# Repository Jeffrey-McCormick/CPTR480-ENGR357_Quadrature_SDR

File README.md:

# CPTR480 Quadrature SDR Hardware Documentation

This repository contains the KiCad schematics, PCB layouts, and Bills of Materials for the CPTR480 Quadrature Software Defined Radio (SDR) receiver board designed by Jeffrey McCormick and Daniel Mendoza for ENGR357 and CPTR480.

**Other contributors**: Riley Smith, Joshua Garbi

## System Architecture

The radio is a direct-conversion, quadrature-sampling receiver (commonly utilizing a Tayloe Detector topology) managed by a Raspberry Pi Pico. The RF front-end downconverts the incoming antenna signal directly to baseband I (In-phase) and Q (Quadrature) audio signals, which are digitized and processed by the RP2040 microcontroller. The board also includes other parts like rotary encoder, OLED display, SD card reader, and DAC for audio output for added functionality. The radio is designed work both on battery power as well as USB power through the Raspberry Pi Pico. The board is designed to be portable and hand-held. 

### Core Hardware Modules

1. **Microcontroller & Digital Core**
   - **Raspberry Pi Pico (RP2040)**: The brains of the SDR. Handles I2C UI/Hardware control, I2S digital audio streams, DSP, and SD card interfacing. The board will support both the original Raspberry Pi Pico board varients and the YD2040 from CPTR480. 

2. **RF Front-End & Mixing (Tayloe Detector)**
   - **SN74CBT3253CDBR**: Dual 1-of-4 FET Multiplexer/Demultiplexer. This high-speed analog switch acts as the quadrature mixer, sequentially sampling the incoming RF signal at the Local Oscillator frequency to produce differential baseband I and Q signals. A second SN74CBT was used for RF filter switching in the front-end.   

   - **SN74AC74DR**: Dual D-Type Positive-Edge-Triggered Flip-Flop, typically used to accurately divide the synthesized clock to drive the Tayloe detector switches with precise 90-degree phase offsets.

3. **Clock Generation**
   - **Si5351A-B-GT**: I2C-programmable ANY-frequency CMOS clock generator. Driven by a high-precision **24.576 MHz TCXO** (ASTX-H11) for ultra-low drift, it synthesizes the Local Oscillator (LO) frequencies. For quadrature mixing, it is configured to output signals at 4x the target listen frequency.

4. **Baseband Amplification**
   - **INA821ID**: High-precision instrumentation amplifiers used to convert the differential outputs of the Tayloe mixer to single-ended signals and apply initial low-noise gain.
   - **OPA1612AxD**: Dual SoundPlus™ high-performance bipolar-input audio operational amplifiers for active low-pass filtering and final baseband gain stages.

5. **Data Converters (Audio/Baseband)**
   - **PCM1808PWR**: 24-bit, 96-kHz Stereo ADC. Digitizes the analog I and Q baseband signals and sends them to the Pico over I2S.
   - **PCM5102A**: 32-bit, 384-kHz Stereo DAC with integrated PLL. Converts the final DSP-processed audio or playback audio from the Pico back to analog for the headphone output.

6. **User Interface**
   - **0.96" OLED Display**: 128x64 pixels, I2C interface.
   - **Rotary Encoder (Alps EC11)**: Includes a push-button switch for frequency tuning and menu navigation.
   - **Tactile Button**: For additional UI control inputs.

7. **Power Management**
   - **TPS7A2045PDQN**: 4.5V Ultra-Low-Noise LDO regulator for sensitive analog components.
   - **TPS72733DSER**: 3.3V Low-Dropout regulator for clean digital/mixed-signal voltage rails.

8. **Connectivity**
   - **BNC Connector (Amphenol)**: Main RF antenna input.
   - **3.5mm Audio Jacks (CUI SJ-3523-SMT)**: For SDR audio output and DAC direct output.
   - **MicroSD Card Slot**: Connected via SPI for playing WAV files or potentially recording IQ streams.

## KiCad Project Structure

The hardware source files are located in the `Radio_Receiver_McCormick_Mendoza` directory. The schematic is built hierarchically:

- **`Radio_Receiver_McCormick_Mendoza.kicad_sch`**: The top-level schematic tying all functional blocks together.
- **`antenna.kicad_sch` / `low_pass_filter.kicad_sch`**: Front-end filtering blocks.
- **`mixer.kicad_sch`**: The Tayloe detector and RF switching core.
- **`clock_generator.kicad_sch`**: Si5351 synthesizer and TCXO.
- **`ADC-24bit.kicad_sch` / `Audio_DAC.kicad_sch`**: Data converter sub-sheets.
- **`raspberry_pi_pico.kicad_sch`**: MCU pinning and decoupling.
- **`power_supply.kicad_sch`**: LDOs and power distribution network.
- **`Display.kicad_sch` / `Angle_Encoder.kicad_sch`**: UI peripherals.

### PCB Images

### Bill of Materials (BOM)

The complete component list, including LCSC part numbers for JLCPCB assembly, can be found in `Radio_Receiver_McCormick_Mendoza.csv`.

## Bring-up and Testing Order

Standalone scripts used during hardware validation. Each can be uploaded and run independently on the board.

| Component | File | Function | Pass/Fail |
|-----------|------|----------|-----------|
| LED | `Bringup/led_blink.py` | Blinks GPIO5 to confirm basic GPIO and upload toolchain | &check; |
| I2C bus | `Bringup/i2c_scan.py` | Scans I2C0 (SDA=12, SCL=13); expects Si5351 at `0x60`, OLED at `0x3C` | &check; |
| OLED display | `Bringup/oled_test.py` | Full exercise suite for the SSD1306 (text, lines, animation, contrast, power cycle) via `ssd1306.py` | &check; |
| Rotary encoder + button | `Bringup/rotary_encoder.py` | `QuadratureEncoder` (detent counting on GPIO 20/21) and `ButtonHandler` (debounced click + long-press on GPIO 22) | &check; |
| Si5351 clock | `Bringup/si5351_test.py` | Register R/W test, PLL lock check, 10.24 MHz quadrature setup, frequency sweep with integer-divider validation | &check; |
| Filter MUX | `Bringup/filter_mux_control.py` | Drives CTL1 (GPIO19) and CTL2 (GPIO18) to select one of four analog filter paths | &check; |
| Si5351 driver | `Bringup/Load_files/si5351.py` | I2C driver: PLL/multiplier config, per-clock dividers, phase offset, output enable | &check; |
| OLED driver | `Bringup/Load_files/ssd1306.py` | Standard MicroPython SSD1306 I2C framebuffer driver | &check; |
| DAC | `Bringup/dac.py` | I2S driver: Configure DAC for stereo or mono playback at 44.1 kHz | &check; |
| ADC | `Bringup/adc.py` | I2S driver: Configure ADC for 16-bit stereo sampling | &cross; |
|  ADC Integration | `Bringup/adc_test.py` | Full duplex loopback test: DAC outputs a sine wave, ADC reads it back, and an LED toggles based on amplitude | &cross; |

**`si5351_test.py` details:** Configures PLLA with N=25 (VCO = 24.576 MHz × 25 = 614.4 MHz), sets CLK0/1/2 dividers, and applies phase offsets of 0°, 90°, and 180° via `set_phase()`. The `is_integer_divider()` helper ensures only frequencies that divide the VCO evenly are programmed during the sweep.

**`rotary_encoder.py` details:** Encoder uses IRQ-driven quadrature decoding with detent aggregation (`ppr` parameter). `ButtonHandler` distinguishes short click (on release before 600 ms) from long press (held ≥ 600 ms); the main app uses long press for "back" navigation.
### Images

## Results

Base Goals

- [x]  Minimum Discernable signal less than 1uV
  - Achieved 1mV
- [ ]  Switching between AM and HF bands
  - Only tested for AM band. 
- [x]  Intuitive interface
  - Got it. See /Software 
- [x]  Portability
   - Battery power works well. Antenna and Board grounds have to be tied together for portable antenna grounding
- [x]  Dual power mode (battery and usb)
   - Got it!! Both work as intended.

 Reach Goals:

- [x]  Low noise (-60dB)
  - Achieved -90dB
  
- [/]  High Image Rejection (-20dB)
- Achieved -15dB to -25dB depending on individual resistor pairs. 
- [ ]  Can record radio signals
   - Unable to test 

### Images

## Future Work

- [ ] Input I and Q signls into pico via ADC 
   - ADC verification 
- [ ] Tracelength matching for Q_LO and I_LO
- [ ] Manufacture optional LP and BP Filters
- [ ] RF signal processing software

### Optional
- [ ] Adding option for lower gain in Intrumentation Amplifier.

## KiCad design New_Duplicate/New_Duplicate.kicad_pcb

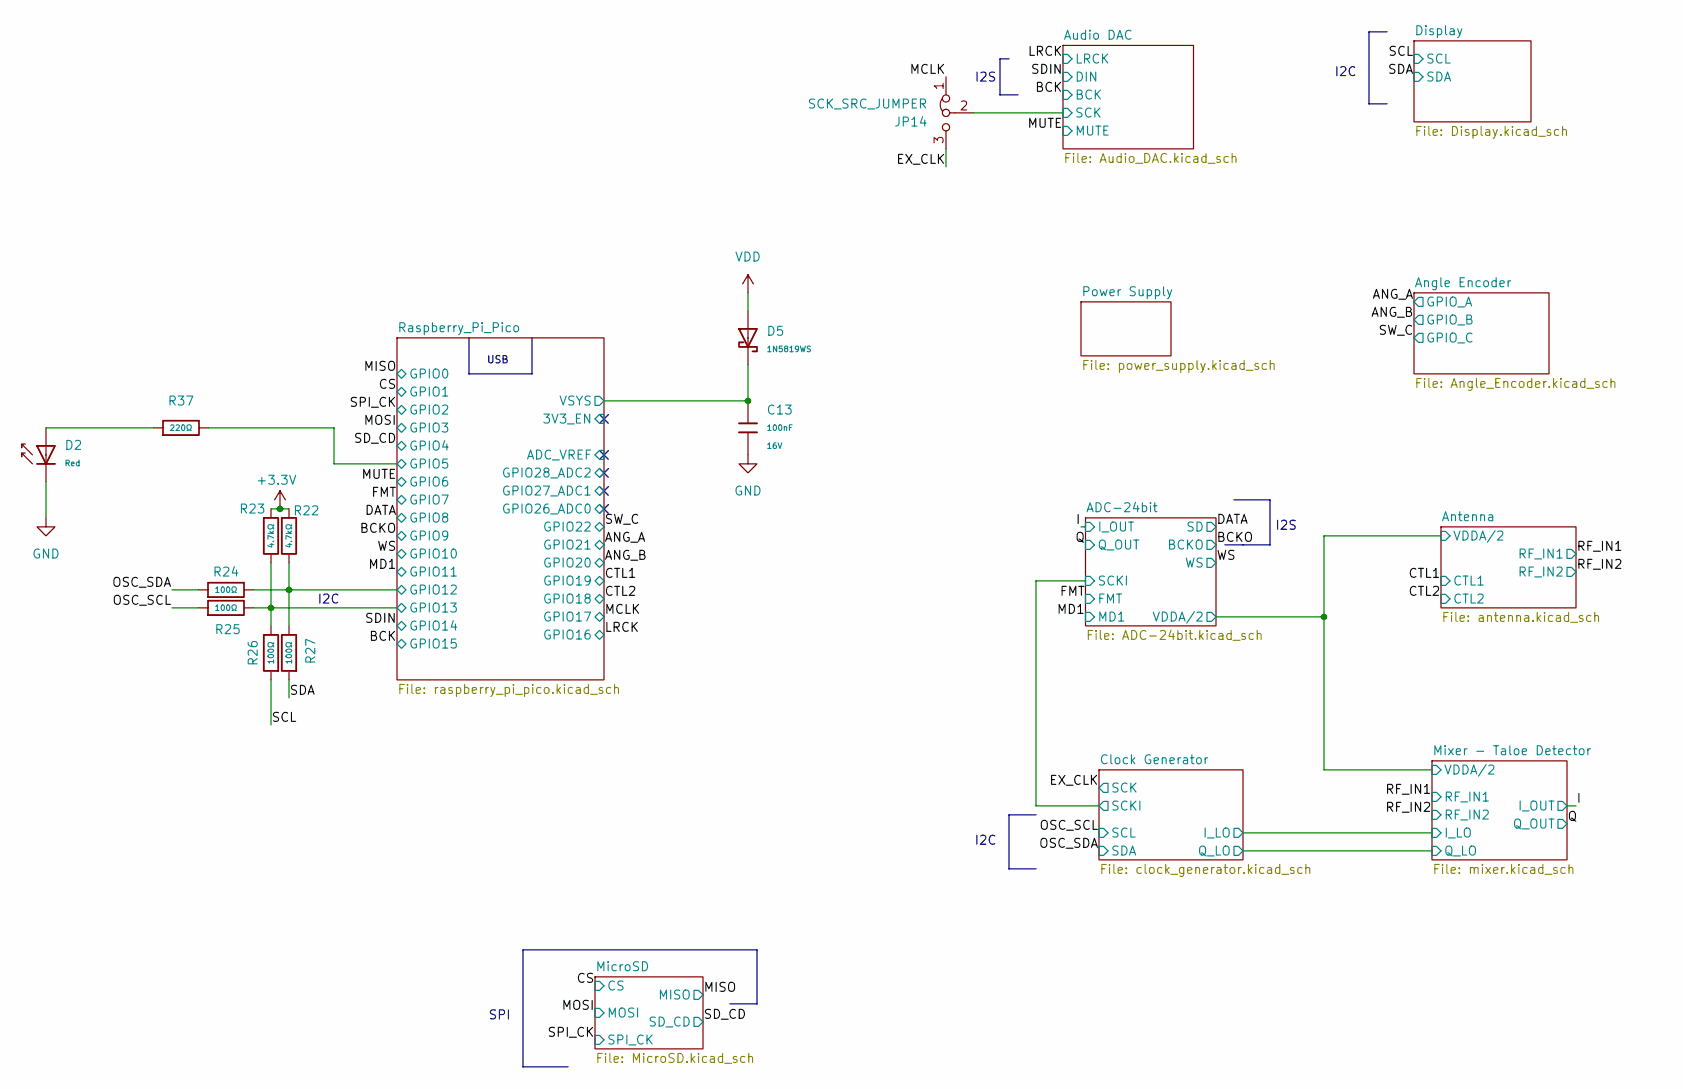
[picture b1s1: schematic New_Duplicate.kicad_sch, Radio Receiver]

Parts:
C13: 100nF; C_0402; Voltage Rated 16V; Tolerance ±10%; Part CL05B104KO5NNNC; LCSC C1525
D2: Red; D_0805; Forward Voltage (VF) 1.6V~2.6V; Part NCD0805R1; LCSC C84256
D5: 1N5819WS; D_SOD-323; Forward Voltage (Vf@If) 600mV@1A; Reverse Voltage (Vr) 40V; Part 1N5819WS; LCSC C191023
JP14: SCK_SRC_JUMPER; SolderJumper-3_P1.3mm_Bridged2Bar12_RoundedPad1.0x1.5mm_Num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
R22, R23: 4.7kΩ; R_0805; Overload Voltage (Max) 150V; Tolerance ±1%; Part 0805W8F4701T5E; LCSC C17673
R24, R25, R26, R27: 100Ω; R_0805; Overload Voltage (Max) 150V; Tolerance ±1%; Part 0805W8F1000T5E; LCSC C17408
R37: 220Ω; R_0603; Overload Voltage (Max) 75V; Tolerance ±1%; Part 0603WAF2200T5E; LCSC C22962

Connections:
+3.3V: R22.1, R23.1; also elsewhere on the board
/Audio DAC/SCK: JP14.2 (C); also elsewhere on the board
/EX_CLK: JP14.3 (B); also elsewhere on the board
/MCLK: JP14.1 (A); also elsewhere on the board
/OSC_SCL: R25.1; also elsewhere on the board
/OSC_SDA: R24.1; also elsewhere on the board
/Raspberry_Pi_Pico/GPIO5: R37.2; also elsewhere on the board
/Raspberry_Pi_Pico/GPIO12: R22.2, R24.2, R27.2; also elsewhere on the board
/Raspberry_Pi_Pico/GPIO13: R23.2, R25.2, R26.2; also elsewhere on the board
/Raspberry_Pi_Pico/VSYS: C13.1, D5.1; also elsewhere on the board
/SCL: R26.1; also elsewhere on the board
/SDA: R27.1; also elsewhere on the board
unnamed: D2.2, R37.1
VDD: D5.2; also elsewhere on the board

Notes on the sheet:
I2S
USB
I2C
SPI

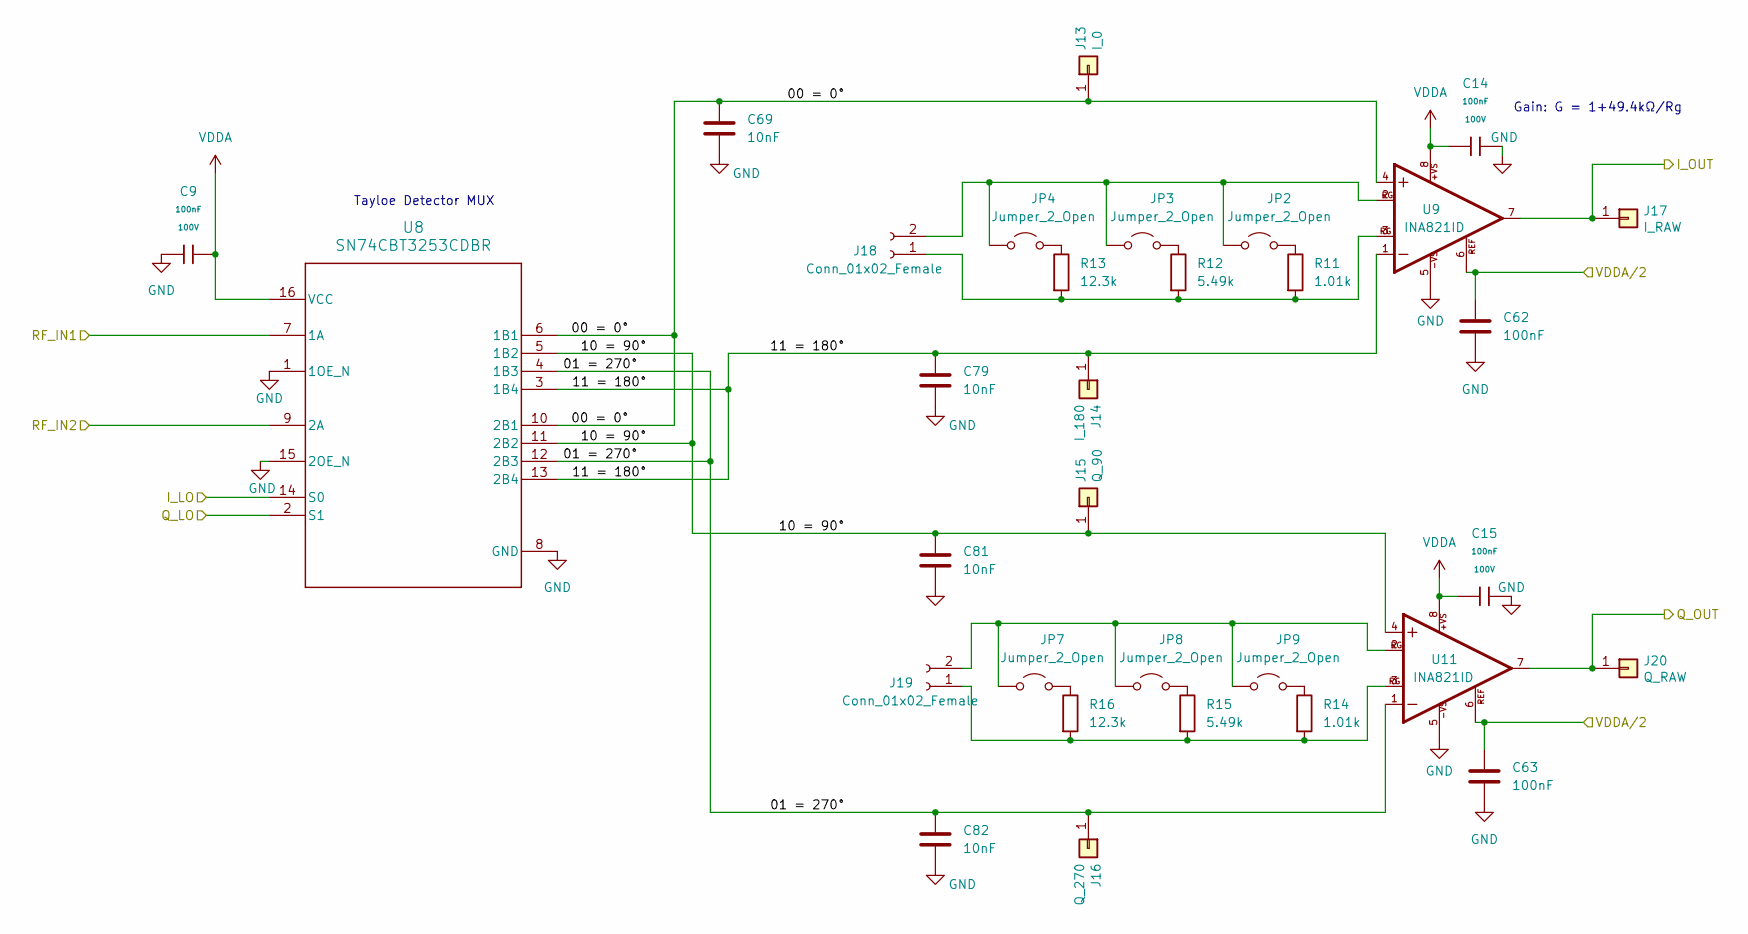
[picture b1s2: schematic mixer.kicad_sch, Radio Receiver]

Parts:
C9, C14, C15: 100nF; C_0805; Voltage Rated 100V; Tolerance ±10%; Part CL21B104KCFNNNE; LCSC C28233
C62, C63: 100nF; C_1206; LCSC C52147198
C69, C79, C81, C82: 10nF; C_0805; LCSC C49326666
J13: I_0; PinHeader_1x01_P2.54mm_Vertical
J14: I_180; PinHeader_1x01_P2.54mm_Vertical
J15: Q_90; PinHeader_1x01_P2.54mm_Vertical
J16: Q_270; PinHeader_1x01_P2.54mm_Vertical
J17: I_RAW; PinHeader_1x01_P2.54mm_Vertical
J18, J19: Conn_01x02_Female; PinSocket_1x02_P2.54mm_Vertical
J20: Q_RAW; PinHeader_1x01_P2.54mm_Vertical
JP2, JP3, JP4, JP7, JP8, JP9: Jumper_2_Open; SolderJumper-2_P1.3mm_Open_RoundedPad1.0x1.5mm
R11, R14: 1.01k; R_0603; LCSC C861188
R12, R15: 5.49k; R_0603; LCSC C861486
R13, R16: 12.3k; R_0603; LCSC C861101
U8: SN74CBT3253CDBR; DB0016A_N; LCSC C2674583
U9, U11: INA821ID; D0008A_N; LCSC C2060822

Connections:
/ADC-24bit/VDDA/2: C62.1, C63.1, U9.6 (REF), U11.6 (REF); also elsewhere on the board
/Clock Generator/I_LO: U8.14 (S0); also elsewhere on the board
/Clock Generator/Q_LO: U8.2 (S1); also elsewhere on the board
/I: J17.1 (Pin_1_1), U9.7 (OUT); also elsewhere on the board
/Mixer - Taloe Detector/00 = 0°: C69.2, J13.1 (Pin_1_1), U8.6 (1B1), U8.10 (2B1), U9.4 (+IN)
/Mixer - Taloe Detector/01 = 270°: C82.2, J16.1 (Pin_1_1), U8.4 (1B3), U8.12 (2B3), U11.1 (-IN)
/Mixer - Taloe Detector/10 = 90°: C81.2, J15.1 (Pin_1_1), U8.5 (1B2), U8.11 (2B2), U11.4 (+IN)
/Mixer - Taloe Detector/11 = 180°: C79.2, J14.1 (Pin_1_1), U8.3 (1B4), U8.13 (2B4), U9.1 (-IN)
/Q: J20.1 (Pin_1_1), U11.7 (OUT); also elsewhere on the board
/RF_IN1: U8.7 (1A); also elsewhere on the board
/RF_IN2: U8.9 (2A); also elsewhere on the board
unnamed: J18.1, R11.2, R12.2, R13.2, U9.3 (RG1)
unnamed: J18.2, JP2.1 (A), JP3.1 (A), JP4.1 (A), U9.2 (RG)
unnamed: J19.1, R14.2, R15.2, R16.2, U11.3 (RG1)
unnamed: J19.2, JP7.1 (A), JP8.1 (A), JP9.1 (A), U11.2 (RG)
unnamed: JP2.2 (B), R11.1
unnamed: JP3.2 (B), R12.1
unnamed: JP4.2 (B), R13.1
unnamed: JP7.2 (B), R16.1
unnamed: JP8.2 (B), R15.1
unnamed: JP9.2 (B), R14.1
VDDA: C9.2, C14.1, C15.1, U8.16 (VCC), U9.8 (+VS), U11.8 (+VS); also elsewhere on the board

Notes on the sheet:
Tayloe Detector MUX
Gain: G = 1+49.4kΩ/Rg

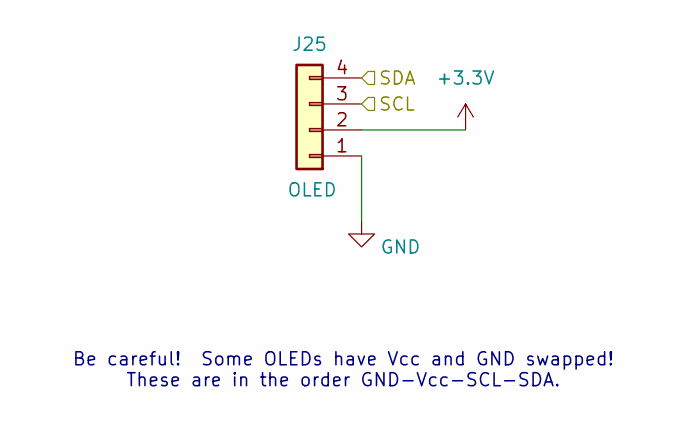
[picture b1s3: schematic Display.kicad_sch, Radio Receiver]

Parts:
J25: OLED; PinSocket_1x04_P2.54mm_Vertical; LCSC C2718488

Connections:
+3.3V: J25.2; also elsewhere on the board
/SCL: J25.3; also elsewhere on the board
/SDA: J25.4; also elsewhere on the board

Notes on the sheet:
Be careful! Some OLEDs have Vcc and GND swapped! These are in the order GND-Vcc-SCL-SDA.

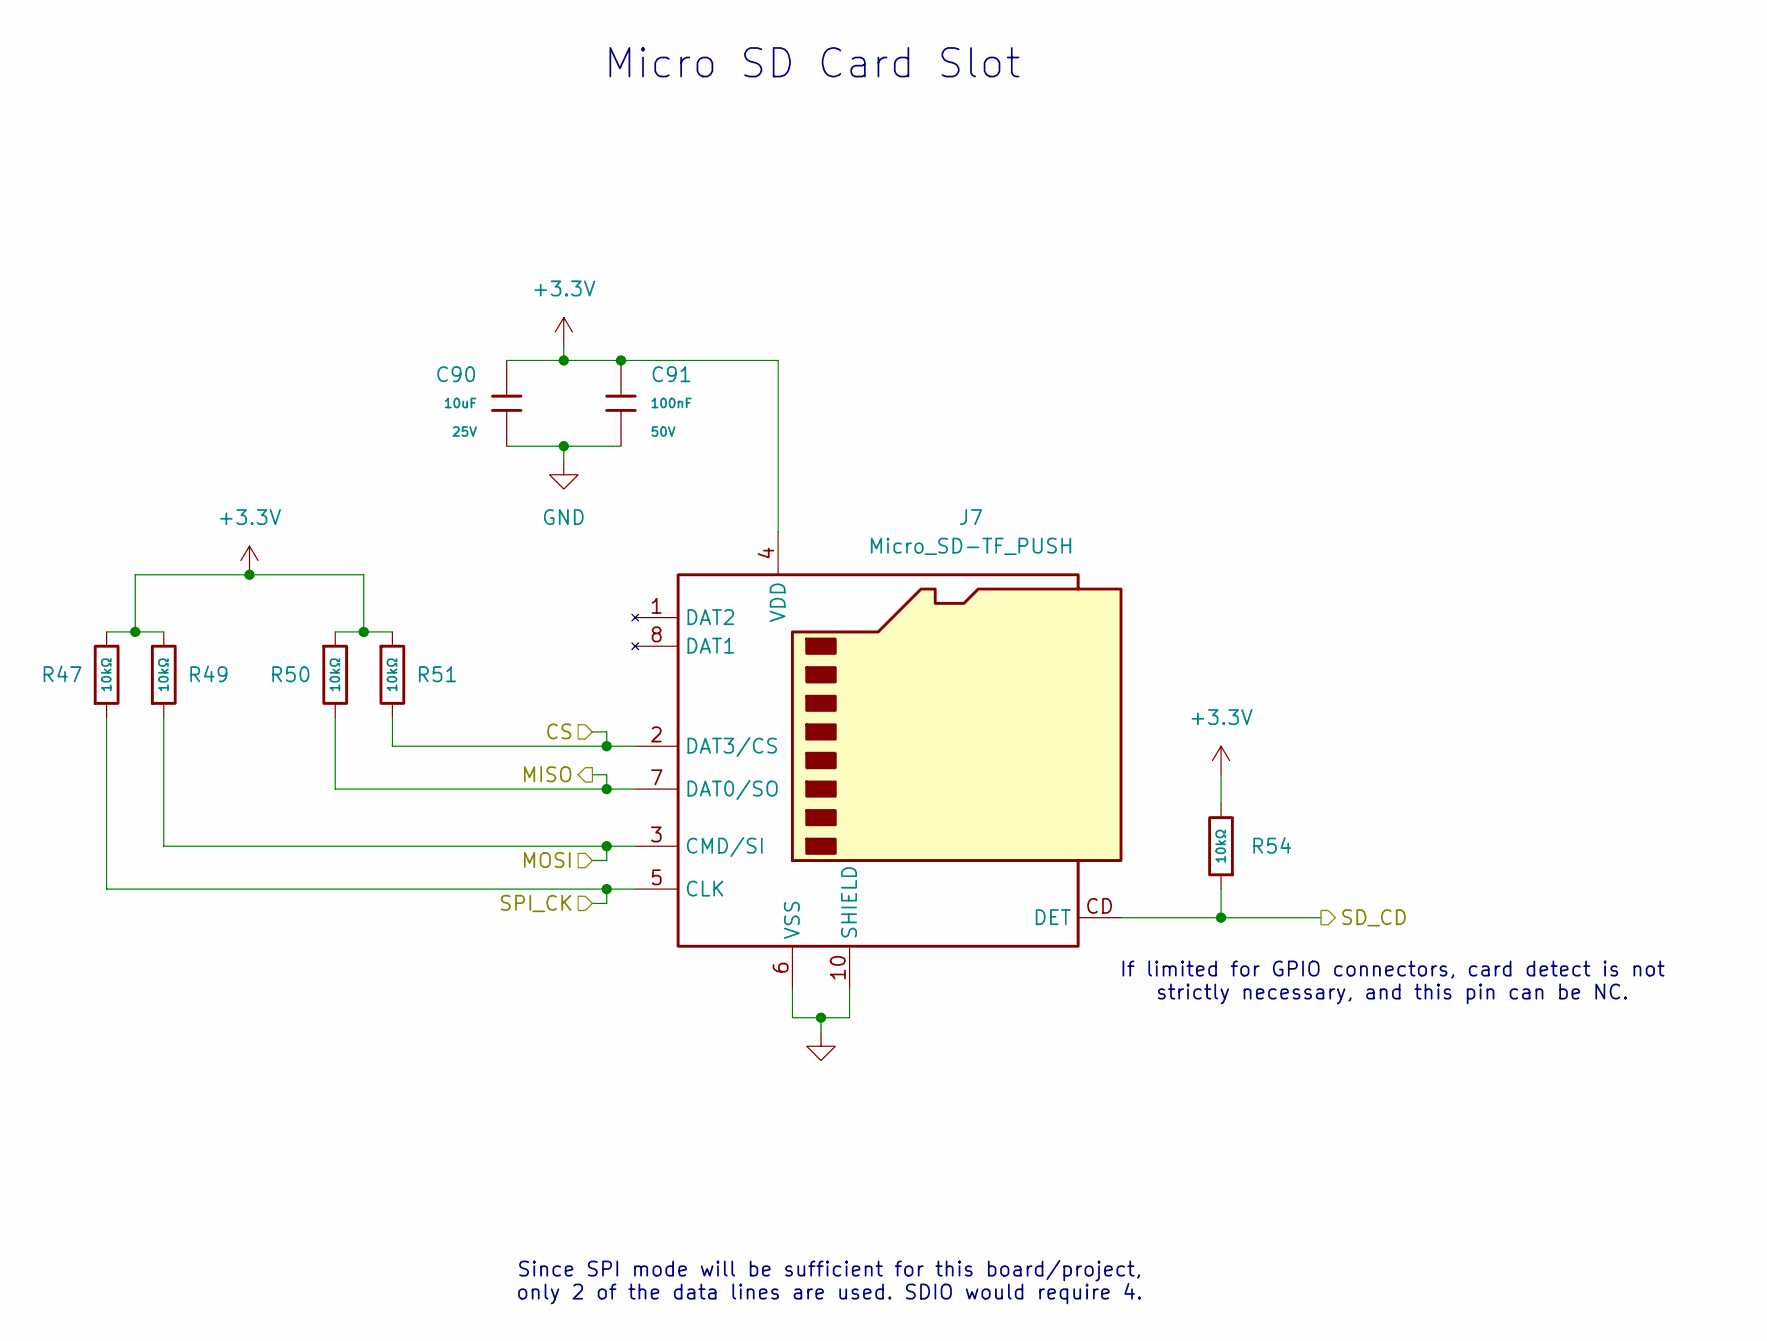
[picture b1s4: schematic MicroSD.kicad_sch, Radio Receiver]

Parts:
C90: 10uF; C_0805; Voltage Rated 25V; Tolerance ±10%; Part CL21A106KAYNNNE; LCSC C15850
C91: 100nF; C_0603; Voltage Rated 50V; Tolerance ±10%; Part CC0603KRX7R9BB104; LCSC C14663
J7: Micro_SD-TF_PUSH; TF-SMD_TF-PUSH; LCSC C393941
R47, R49, R50, R51, R54: 10kΩ; R_0603; Overload Voltage (Max) 75V; Tolerance ±1%; Part 0603WAF1002T5E; LCSC C25804

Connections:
+3.3V: C90.1, C91.1, J7.4 (VDD), R47.2, R49.2, R50.1, R51.1, R54.2; also elsewhere on the board
/CS: J7.2 (DAT3/CS), R51.2; also elsewhere on the board
/MISO: J7.7 (DAT0/SO), R50.2; also elsewhere on the board
/MOSI: J7.3 (CMD/SI), R49.1; also elsewhere on the board
/SD_CD: J7.CD (DET), R54.1; also elsewhere on the board
/SPI_CK: J7.5 (CLK), R47.1; also elsewhere on the board

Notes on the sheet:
Since SPI mode will be sufficient for this board/project, only 2 of the data lines are used. SDIO would require 4.
Micro SD Card Slot
If limited for GPIO connectors, card detect is not strictly necessary, and this pin can be NC.

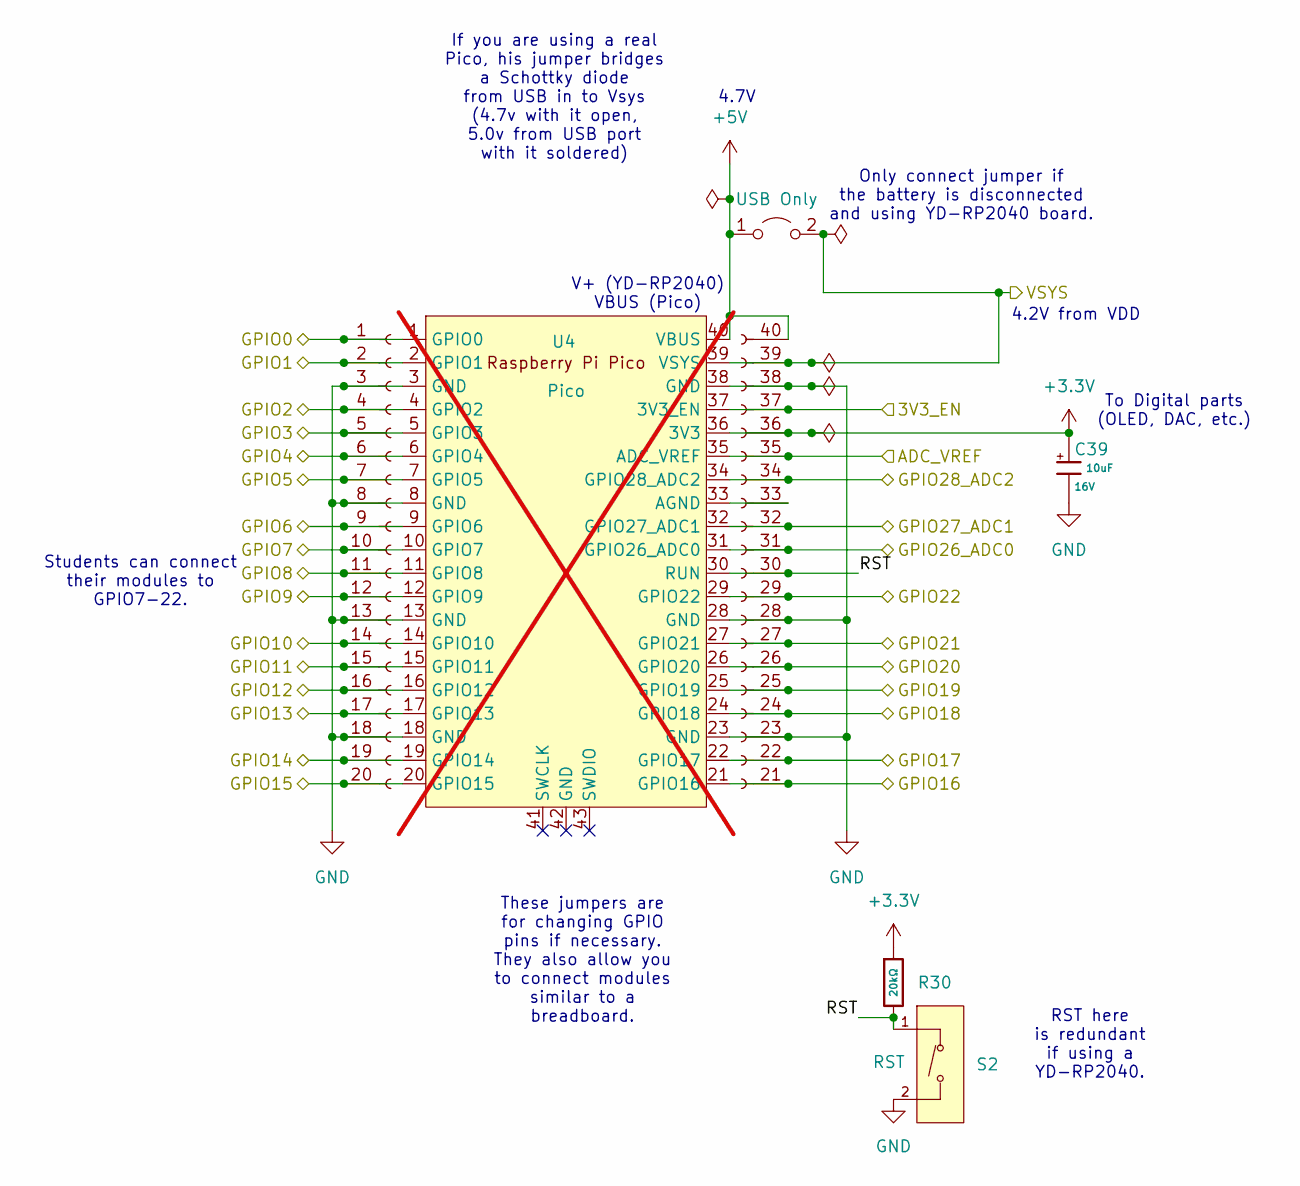
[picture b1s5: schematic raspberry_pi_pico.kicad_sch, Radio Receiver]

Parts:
C39: 10uF; C_CASE-A-3216-18(mm); Tolerance ±10%; Rated Voltage 16V; Part TAJA106K016RNJ; LCSC C7171
J27, J29: Conn_01x20_Socket; LCSC C2905423
JP69: USB Only; SolderJumper-2_P1.3mm_Open_RoundedPad1.0x1.5mm
R30: 20kΩ; R_0805; Overload Voltage (Max) 150V; Tolerance ±1%; Part 0805W8F2002T5E; LCSC C4328
S2: Tactile Button, 160gf; SW_TS-1088-AR02016; Voltage Rating (Dc) 12V; Part TS-1088-AR02016; LCSC C720477
U4: Pico; RPi_Pico_SMD_TH; not fitted

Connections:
+3.3V: C39.1, J29.36 (Pin_5), R30.1, U4.36 (3V3); also elsewhere on the board
+5V: J29.40 (Pin_1), JP69.1 (A), U4.40 (VBUS); also elsewhere on the board
/ANG_A: J29.27 (Pin_14), U4.27 (GPIO21); also elsewhere on the board
/ANG_B: J29.26 (Pin_15), U4.26 (GPIO20); also elsewhere on the board
/BCK: J27.20, U4.20 (GPIO15); also elsewhere on the board
/BCKO: J27.12, U4.12 (GPIO9); also elsewhere on the board
/CS: J27.2, U4.2 (GPIO1); also elsewhere on the board
/CTL1: J29.25 (Pin_16), U4.25 (GPIO19); also elsewhere on the board
/CTL2: J29.24 (Pin_17), U4.24 (GPIO18); also elsewhere on the board
/DATA: J27.11, U4.11 (GPIO8); also elsewhere on the board
/FMT: J27.10, U4.10 (GPIO7); also elsewhere on the board
/LRCK: J29.21 (Pin_20), U4.21 (GPIO16); also elsewhere on the board
/MCLK: J29.22 (Pin_19), U4.22 (GPIO17); also elsewhere on the board
/MD1: J27.15, U4.15 (GPIO11); also elsewhere on the board
/MISO: J27.1, U4.1 (GPIO0); also elsewhere on the board
/MOSI: J27.5, U4.5 (GPIO3); also elsewhere on the board
/MUTE: J27.9, U4.9 (GPIO6); also elsewhere on the board
/Raspberry_Pi_Pico/3V3_EN: J29.37 (Pin_4), U4.37 (3V3_EN)
/Raspberry_Pi_Pico/ADC_VREF: J29.35 (Pin_6), U4.35 (ADC_VREF)
/Raspberry_Pi_Pico/GPIO5: J27.7, U4.7 (GPIO5); also elsewhere on the board
/Raspberry_Pi_Pico/GPIO12: J27.16, U4.16 (GPIO12); also elsewhere on the board
/Raspberry_Pi_Pico/GPIO13: J27.17, U4.17 (GPIO13); also elsewhere on the board
/Raspberry_Pi_Pico/GPIO26_ADC0: J29.31 (Pin_10), U4.31 (GPIO26_ADC0)
/Raspberry_Pi_Pico/GPIO27_ADC1: J29.32 (Pin_9), U4.32 (GPIO27_ADC1)
/Raspberry_Pi_Pico/GPIO28_ADC2: J29.34 (Pin_7), U4.34 (GPIO28_ADC2)
/Raspberry_Pi_Pico/RST: J29.30 (Pin_11), R30.2, S2.1 (A), U4.30 (RUN)
/Raspberry_Pi_Pico/VSYS: J29.39 (Pin_2), JP69.2 (B), U4.39 (VSYS); also elsewhere on the board
/SDIN: J27.19, U4.19 (GPIO14); also elsewhere on the board
/SD_CD: J27.6, U4.6 (GPIO4); also elsewhere on the board
/SPI_CK: J27.4, U4.4 (GPIO2); also elsewhere on the board
/SW_C: J29.29 (Pin_12), U4.29 (GPIO22); also elsewhere on the board
/WS: J27.14, U4.14 (GPIO10); also elsewhere on the board
unnamed: J29.33 (Pin_8), U4.33 (AGND)

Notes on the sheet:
Only connect jumper if the battery is disconnected and using YD-RP2040 board.
V+ (YD-RP2040) VBUS (Pico)
4.7V
4.2V from VDD
If you are using a real Pico, his jumper bridges a Schottky diode from USB in to Vsys (4.7v with it open, 5.0v from USB port with it soldered)
To Digital parts (OLED, DAC, etc.)
RST here is redundant if using a YD-RP2040.
Students can connect their modules to GPIO7-22.
These jumpers are for changing GPIO pins if necessary. They also allow you to connect modules similar to a breadboard.

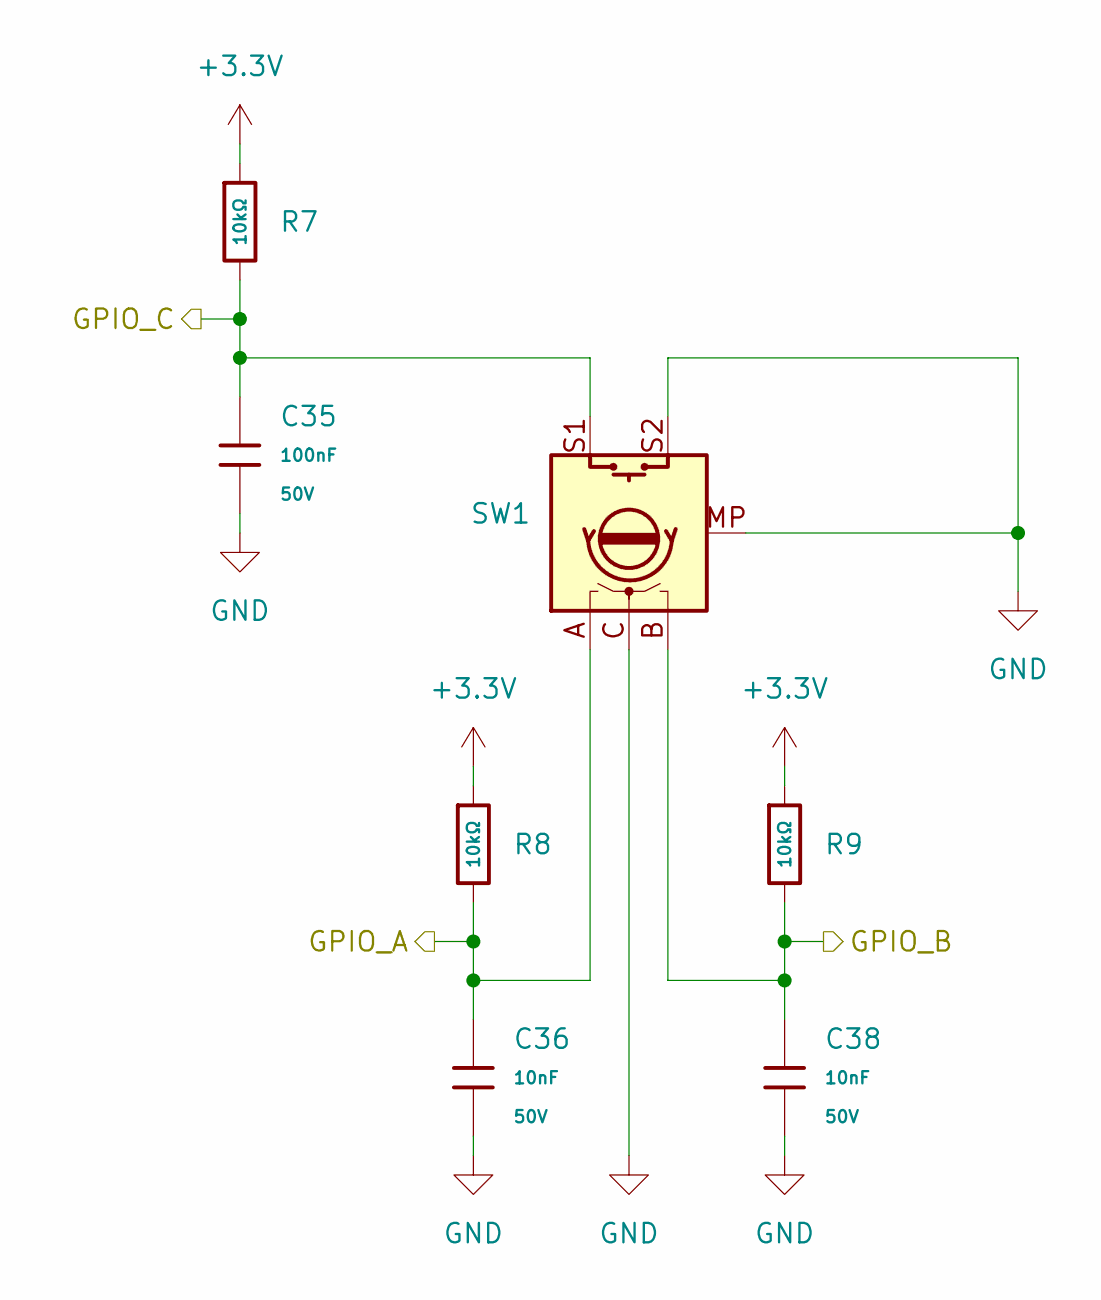
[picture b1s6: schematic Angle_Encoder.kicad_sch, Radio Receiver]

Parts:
C35: 100nF; C_0402; Voltage Rated 50V; Tolerance ±10%; Part CL05B104KB54PNC; LCSC C307331
C36, C38: 10nF; C_0402; Voltage Rated 50V; Tolerance ±10%; Part CL05B103KB5NNNC; LCSC C15195
R7, R8, R9: 10kΩ; R_0402; Overload Voltage (Max) 50V; Tolerance ±1%; Part 0402WGF1002TCE; LCSC C25744
SW1: RotaryEncoder_Switch_MP; RotaryEncoder_Alps_EC11E-Switch_Vertical_H20mm; LCSC C202365

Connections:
+3.3V: R7.1, R8.1, R9.1; also elsewhere on the board
/ANG_A: C36.1, R8.2, SW1.A; also elsewhere on the board
/ANG_B: C38.1, R9.2, SW1.B; also elsewhere on the board
/SW_C: C35.1, R7.2, SW1.S1; also elsewhere on the board

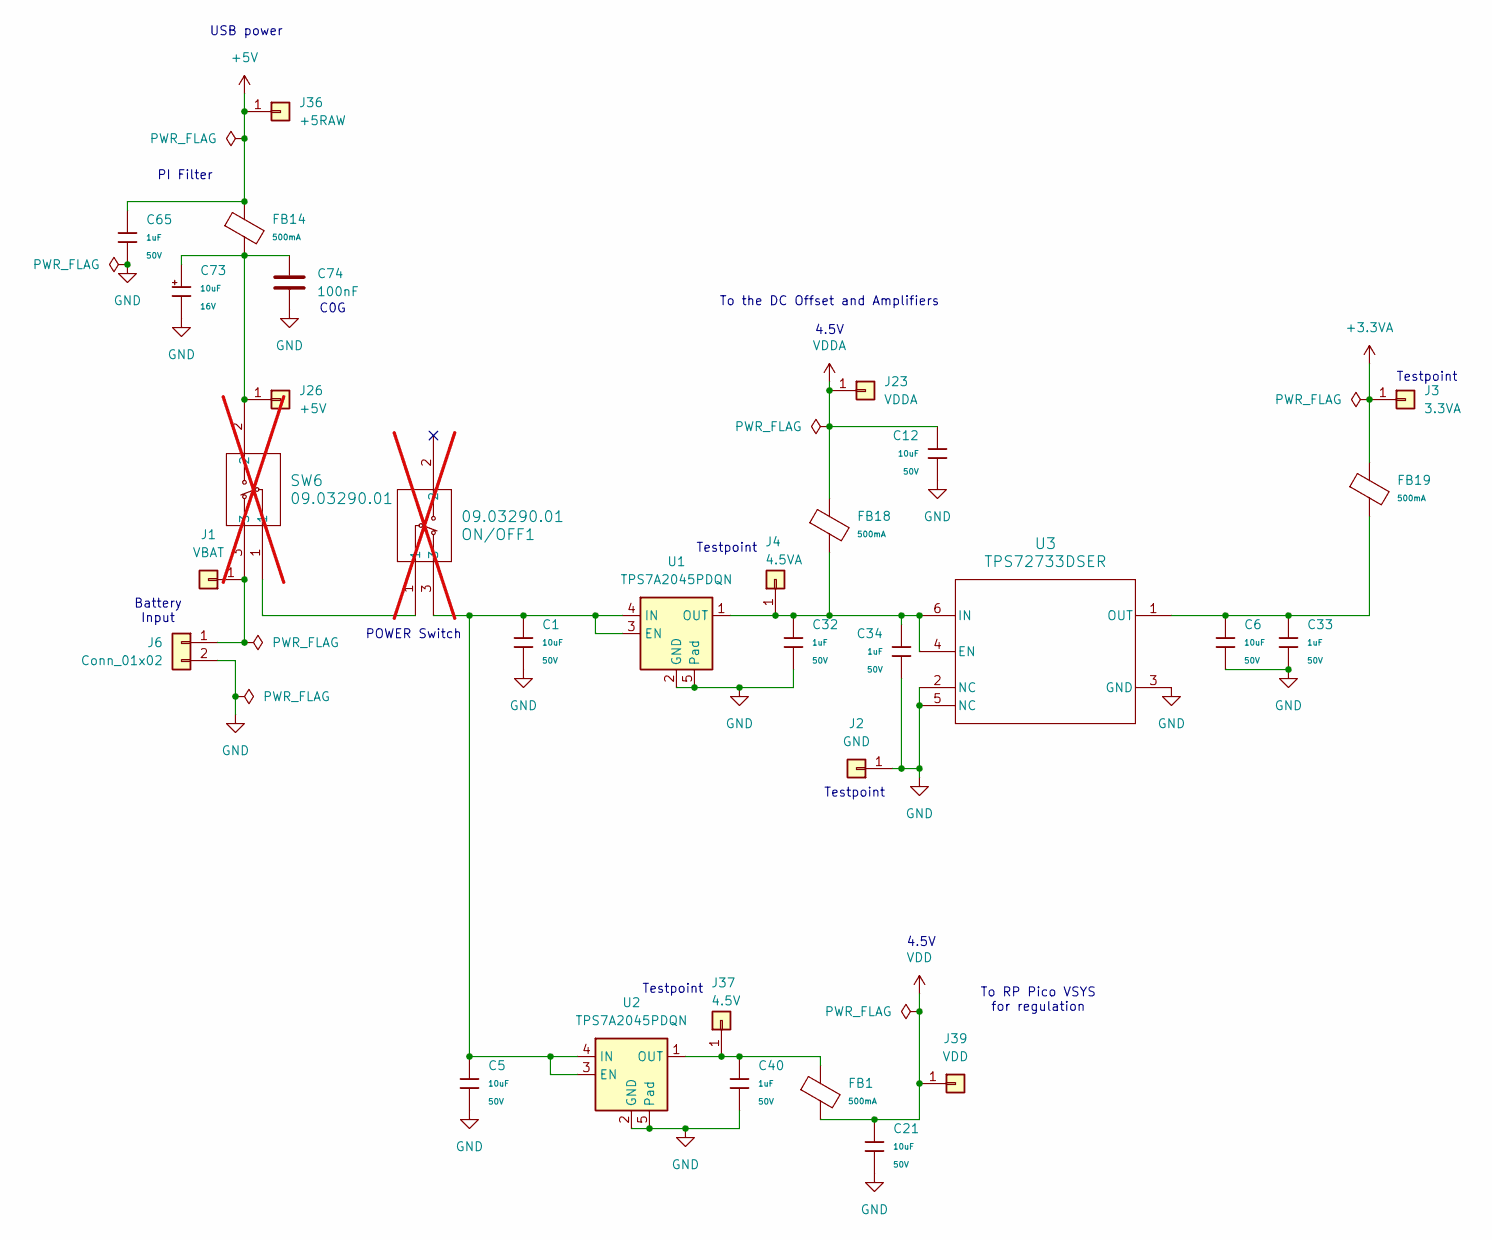
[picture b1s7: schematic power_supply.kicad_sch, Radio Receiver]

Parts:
C1, C5, C6, C12, C21: 10uF; C_0805; Voltage Rated 50V; Tolerance ±10%; Part GRM21BR61H106KE43L; LCSC C440198
C32, C33, C34, C40, C65: 1uF; C_0603; Voltage Rated 50V; Tolerance ±10%; Part CL10A105KB8NNNC; LCSC C15849
C73: 10uF; C_CASE-A-3216-18(mm); Tolerance ±10%; Rated Voltage 16V; Part TAJA106K016RNJ; LCSC C7171
C74: 100nF; C_1206; LCSC C52147198
FB1, FB14, FB18, FB19: FB_0805; Current Rating 500mA; Tolerance ±25%; Part GZ2012D601TF; LCSC C1017
J1: VBAT; PinHeader_1x01_P2.54mm_Vertical
J2: GND; PinHeader_1x01_P2.54mm_Vertical
J3: 3.3VA; PinHeader_1x01_P2.54mm_Vertical
J4: 4.5VA; PinHeader_1x01_P2.54mm_Vertical
J6: Conn_01x02; PinHeader_1x02_P2.54mm_Vertical
J23: VDDA; PinHeader_1x01_P2.54mm_Vertical
J26: +5V; PinHeader_1x01_P2.54mm_Vertical
J36: +5RAW; PinHeader_1x01_P2.54mm_Vertical
J37: 4.5V; PinHeader_1x01_P2.54mm_Vertical
J39: VDD; PinHeader_1x01_P2.54mm_Vertical
ON/OFF1: 09.03290.01; 09.03290_EAO; not fitted
SW6: 09.03290.01; 09.03290_EAO; not fitted
U1, U2: TPS7A2045PDQN; Texas_X2SON-4_1x1mm_P0.65mm; LCSC C3752275
U3: TPS72733DSER; DSE0006A; LCSC C544524

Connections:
+5V: C65.1, FB14.1, J36.1 (Pin_1_1); also elsewhere on the board
unnamed: J1.1 (Pin_1_1), J6.1, SW6.3
unnamed: C32.1, C34.2, FB18.2, J4.1 (Pin_1_1), U1.1 (OUT), U3.4 (EN), U3.6 (IN)
unnamed: C73.1, C74.1, FB14.2, J26.1 (Pin_1_1), SW6.2
unnamed: C40.1, FB1.1, J37.1 (Pin_1_1), U2.1 (OUT)
unnamed: ON/OFF1.1, SW6.1
unnamed: C1.1, C5.1, ON/OFF1.3, U1.3 (EN), U1.4 (IN), U2.3 (EN), U2.4 (IN)
unnamed: C6.1, C33.1, FB19.2, U3.1 (OUT)
VDD: C21.1, FB1.2, J39.1 (Pin_1_1); also elsewhere on the board
VDDA: C12.1, FB18.1, J23.1 (Pin_1_1); also elsewhere on the board

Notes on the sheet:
4.5V
USB power
Testpoint
POWER Switch
Battery Input
C0G
To the DC Offset and Amplifiers
To RP Pico VSYS for regulation
PI Filter
